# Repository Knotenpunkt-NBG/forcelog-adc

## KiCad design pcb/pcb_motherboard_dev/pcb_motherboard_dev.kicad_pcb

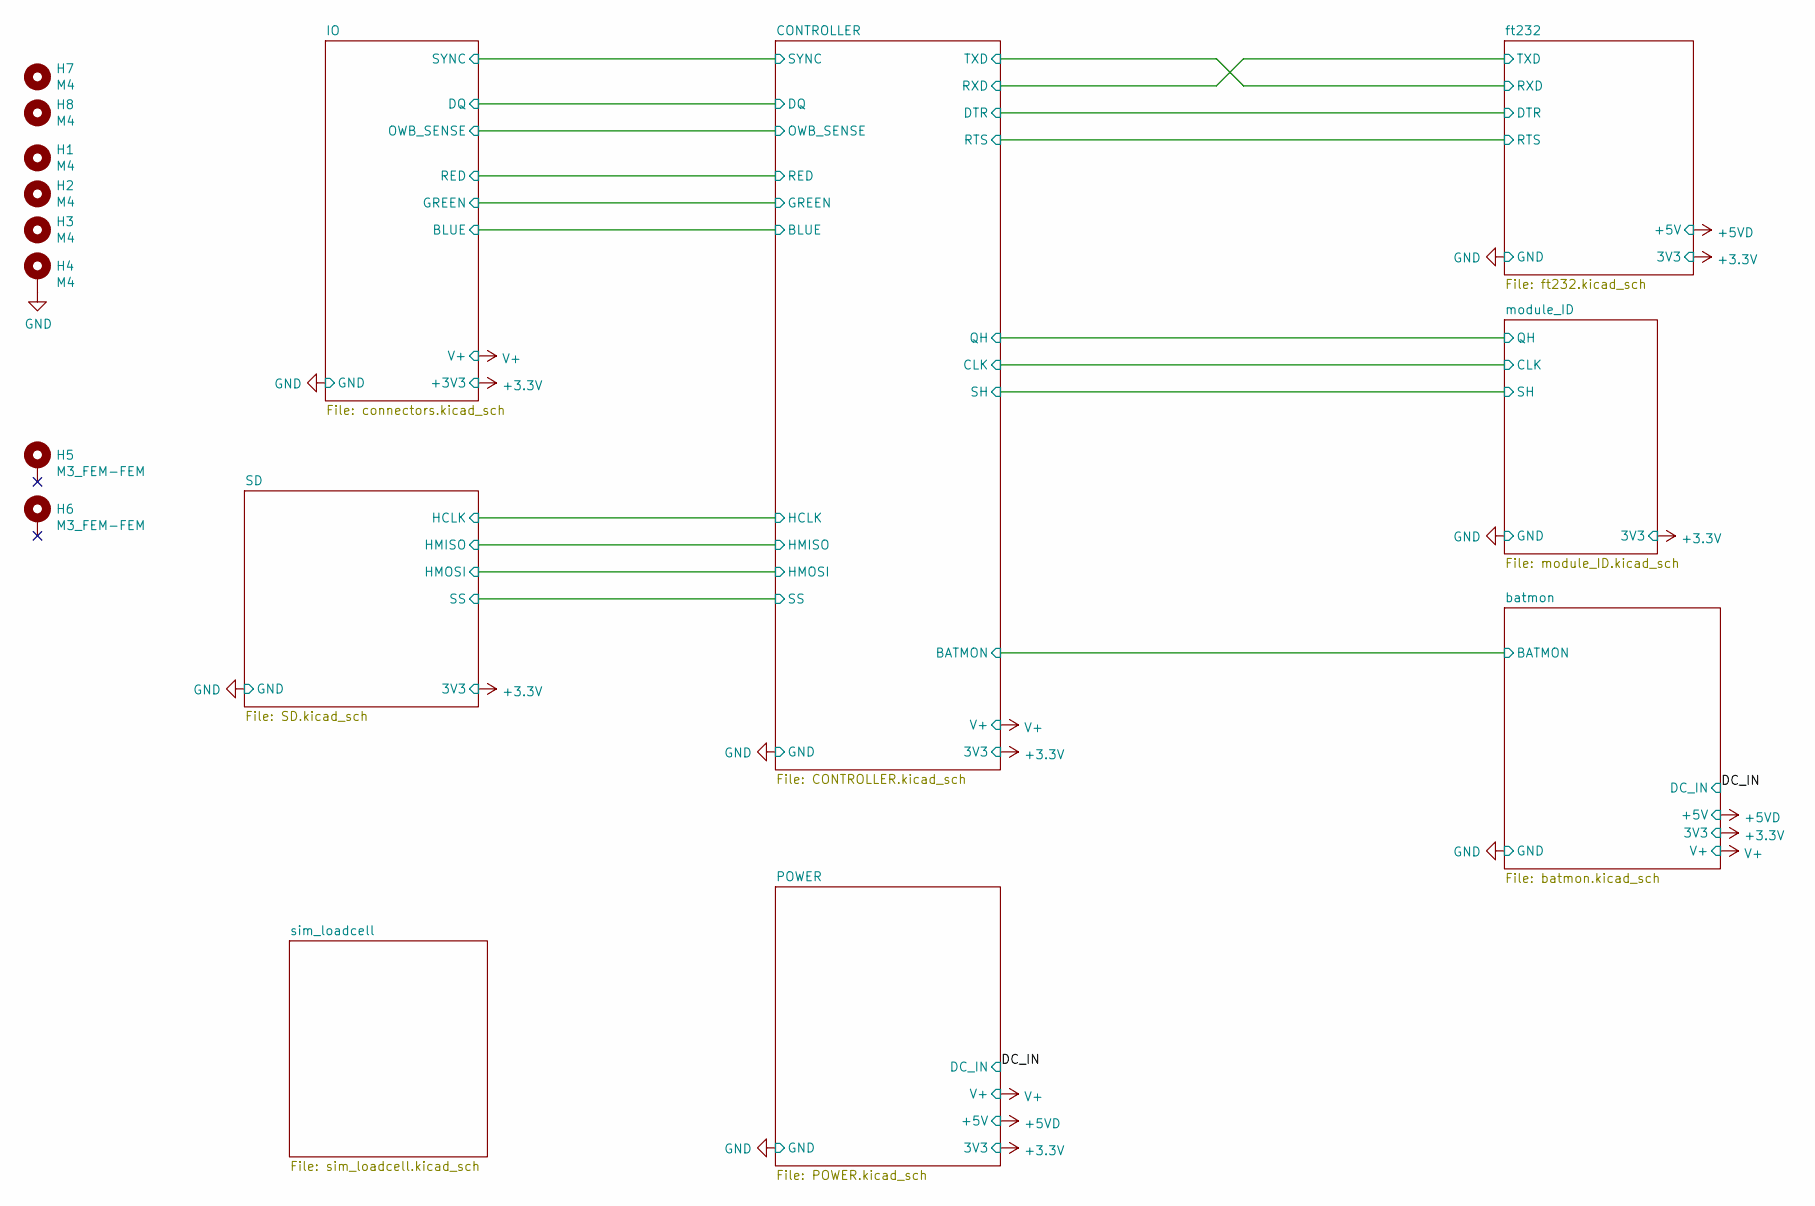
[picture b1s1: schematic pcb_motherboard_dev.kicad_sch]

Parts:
H1, H7: M4; MountingHole_4.3mm_M4_Pad_Via
H2, H3, H4, H8: M4; MountingHole_3.2mm_M3_Pad_Via
H5, H6: M3_FEM-FEM; MountingHole_3.2mm_M3_Pad_Via

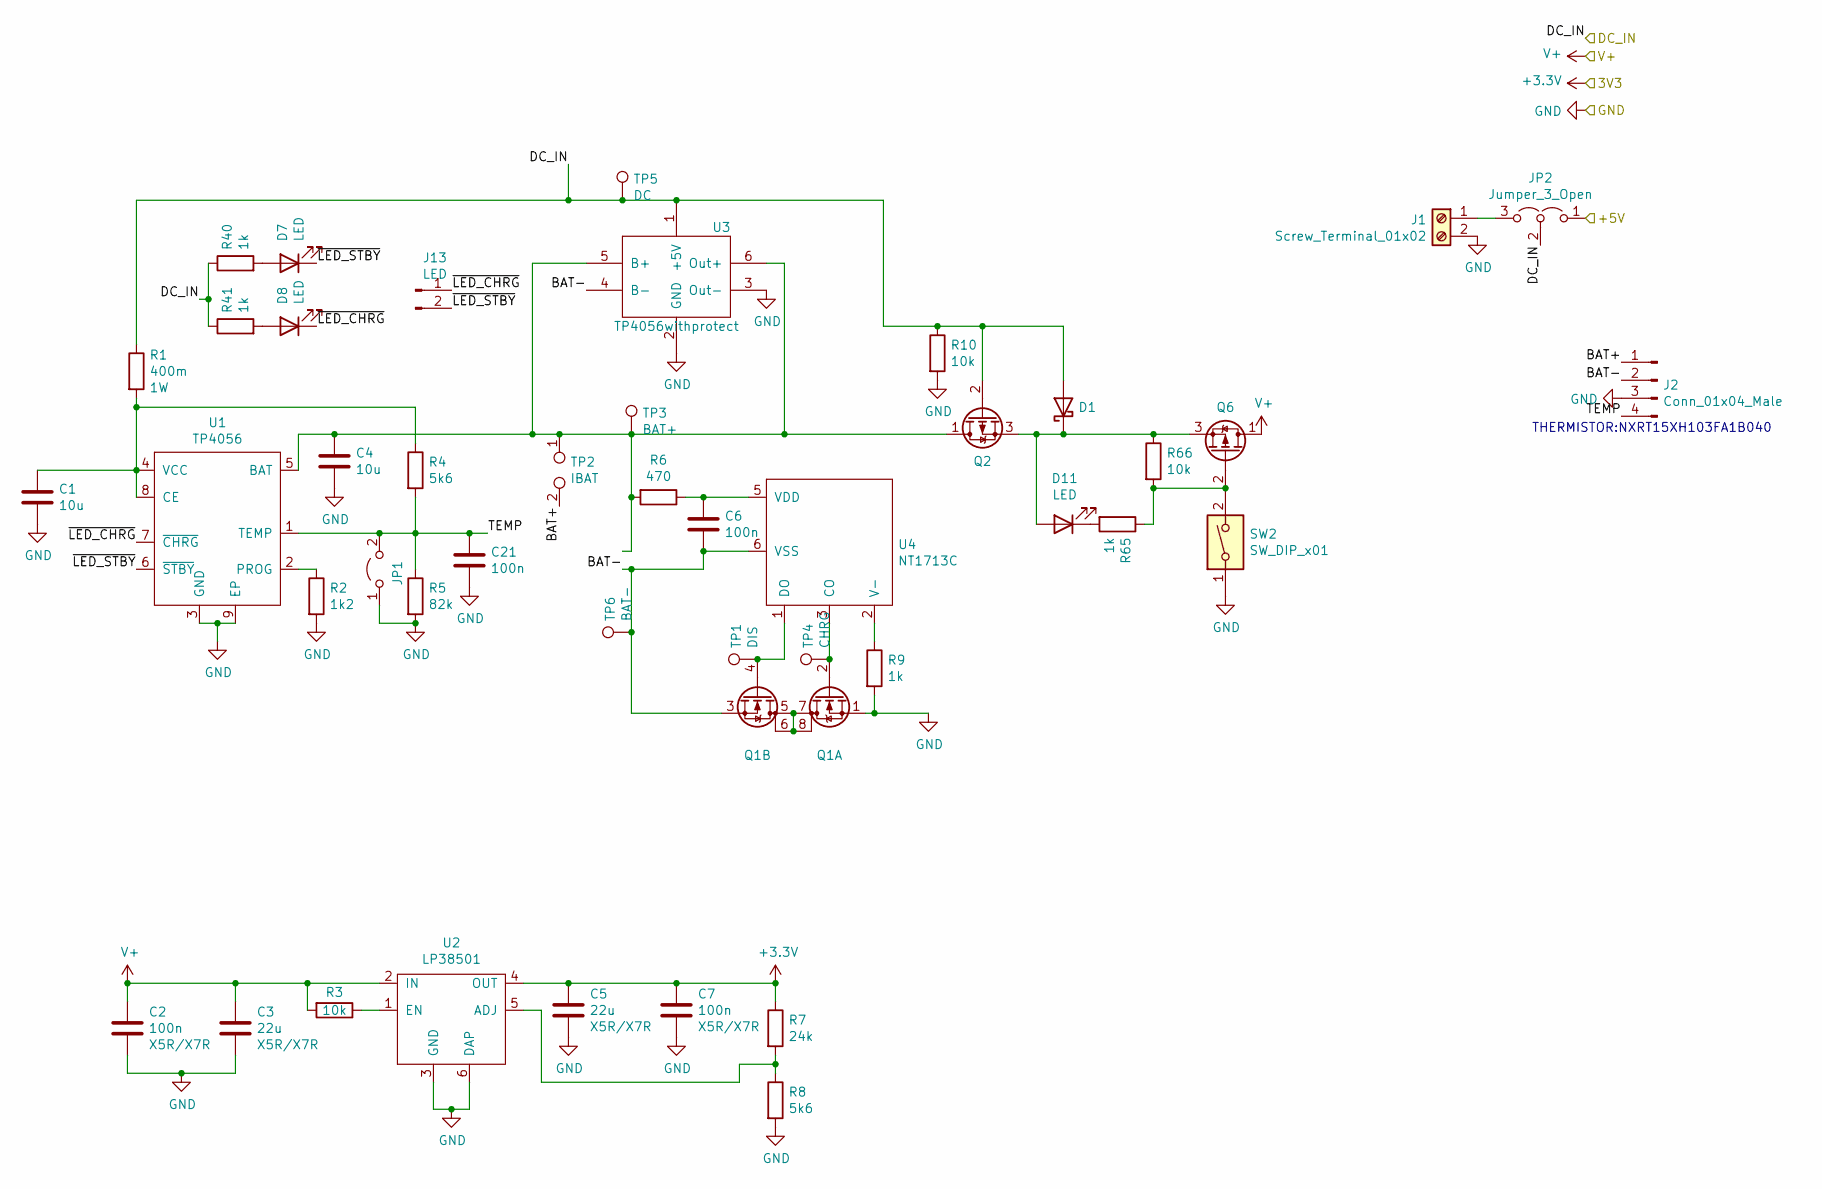
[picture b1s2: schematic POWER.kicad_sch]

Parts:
C1, C4: 10u; C_1206_3216Metric_Pad1.33x1.80mm_HandSolder; Digikey 1276-1075-1-ND
C2, C6, C7, C21: 100n; C_1206_3216Metric_Pad1.33x1.80mm_HandSolder; Digikey 399-C1206C104K5RAC7800CT-ND
C3, C5: 22u; C_1206_3216Metric_Pad1.33x1.80mm_HandSolder; Digikey 1276-2728-1-ND
D1: PMEG3030EP,115; D_SOD-128; Digikey 1727-5324-1-ND
D7, D11: LED; LED_1206_3216Metric_Pad1.42x1.75mm_HandSolder; Digikey 732-5032-1-ND
D8: LED; LED_1206_3216Metric_Pad1.42x1.75mm_HandSolder; Digikey 732-5034-1-ND
J1: Screw_Terminal_01x02; TerminalBlock_Phoenix_MKDS-1,5-2_1x02_P5.00mm_Horizontal; Digikey 277-16667-ND
J2: Conn_01x04_Male; JST_XH_S4B-XH-A-1_1x04_P2.50mm_Horizontal; Digikey 455-4227-ND
J13: LED; TestPoint_2Pads_Pitch2.54mm_Drill0.8mm
JP1: Jumper_2_Open; PinHeader_1x02_P2.54mm_Vertical
JP2: Jumper_3_Open; PinHeader_1x03_P2.54mm_Vertical
Q1: DMG9926USD; SO-8_3.9x4.9mm_P1.27mm; Digikey DMG9926USD-13DICT-ND
Q2, Q6: IRF7410TRPBF; SO8_3.8x4.8_SSSGDDDD; Digikey IRF7410TRPBF
R1: 400m; R_2512_6332Metric_Pad1.40x3.35mm_HandSolder; LCSC C165323
R2: 1k2; R_1206_3216Metric_Pad1.30x1.75mm_HandSolder; LCSC C185265
R3, R10, R66: 10k; R_1206_3216Metric_Pad1.30x1.75mm_HandSolder; LCSC C132649
R4, R8: 5k6; R_1206_3216Metric_Pad1.30x1.75mm_HandSolder; LCSC C137248
R5: 82k; R_1206_3216Metric_Pad1.30x1.75mm_HandSolder; LCSC C137229
R6: 470; R_1206_3216Metric_Pad1.30x1.75mm_HandSolder; LCSC C114945
R7: 24k; R_1206_3216Metric_Pad1.30x1.75mm_HandSolder; LCSC C163384
R9, R40, R41, R65: 1k; R_1206_3216Metric_Pad1.30x1.75mm_HandSolder; LCSC C131398
SW2: SW_DIP_x01; SW_DIP_SPSTx01_Slide_9.78x4.72mm_W7.62mm_P2.54mm; LCSC C229812
TP1: DIS; PinHeader_1x01_P2.54mm_Vertical
TP2: IBAT; PinHeader_1x02_P2.54mm_Vertical
TP3: BAT+; PinHeader_1x01_P2.54mm_Vertical
TP4: CHRG; PinHeader_1x01_P2.54mm_Vertical
TP5: DC; PinHeader_1x01_P2.54mm_Vertical
TP6: BAT-; PinHeader_1x01_P2.54mm_Vertical
U1: TP4056; SOIC-8-1EP_3.9x4.9mm_P1.27mm_EP2.29x3mm_ThermalVias; LCSC C191323
U2: LP38501; TO-263-5_TabPin6; LCSC C779671
U3: TP4056withprotect; TP4056_module_prot; Digikey N/A
U4: NT1713C; SOT-23-6_Handsoldering; LCSC C596362

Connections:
+5V: JP2.1 (A); also elsewhere on the board
/DC_IN: D1.2 (A), JP2.2 (C), Q2.2 (G), R1.1, R10.1, R40.1, R41.1, TP5.1, U3.1 (+5V); also elsewhere on the board
/POWER/BAT+: J2.1, TP2.2
/POWER/BAT-: C6.2, J2.2, Q1.3 (S), TP6.1, U3.4 (B-), U4.6 (VSS)
/POWER/TEMP: C21.1, J2.4, JP1.2 (B), R4.2, R5.1, U1.1 (TEMP)
/POWER/~LED_CHRG: D8.1 (K), J13.1, U1.7 (~CHRG)
/POWER/~LED_STBY: D7.1 (K), J13.2, U1.6 (~STBY)
unnamed: C1.1, R1.2, R4.1, U1.4 (VCC), U1.8 (CE)
unnamed: C4.1, Q2.1 (D), R6.2, TP2.1, TP3.1, U1.5 (BAT), U3.5 (B+), U3.6 (Out+)
unnamed: C6.1, R6.1, U4.5 (VDD)
unnamed: D1.1 (K), D11.2 (A), Q2.3 (S), Q6.3 (S), R66.1
unnamed: D7.2 (A), R40.2
unnamed: D8.2 (A), R41.2
unnamed: D11.1 (K), R65.2
unnamed: J1.1, JP2.3 (B)
unnamed: Q1.2 (G), TP4.1, U4.3 (CO)
unnamed: Q1.4 (G), TP1.1, U4.1 (DO)
unnamed: Q1.5 (D), Q1.6 (D), Q1.7 (D), Q1.8 (D)
unnamed: Q6.2 (G), R65.1, R66.2, SW2.2
unnamed: R2.1, U1.2 (PROG)
unnamed: R3.1, U2.1 (EN)
unnamed: R7.2, R8.1, U2.5 (ADJ)
unnamed: R9.1, U4.2 (V-)
V+: C2.1, C3.1, Q6.1 (D), R3.2, U2.2 (IN); also elsewhere on the board

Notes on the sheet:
THERMISTOR:NXRT15XH103FA1B040

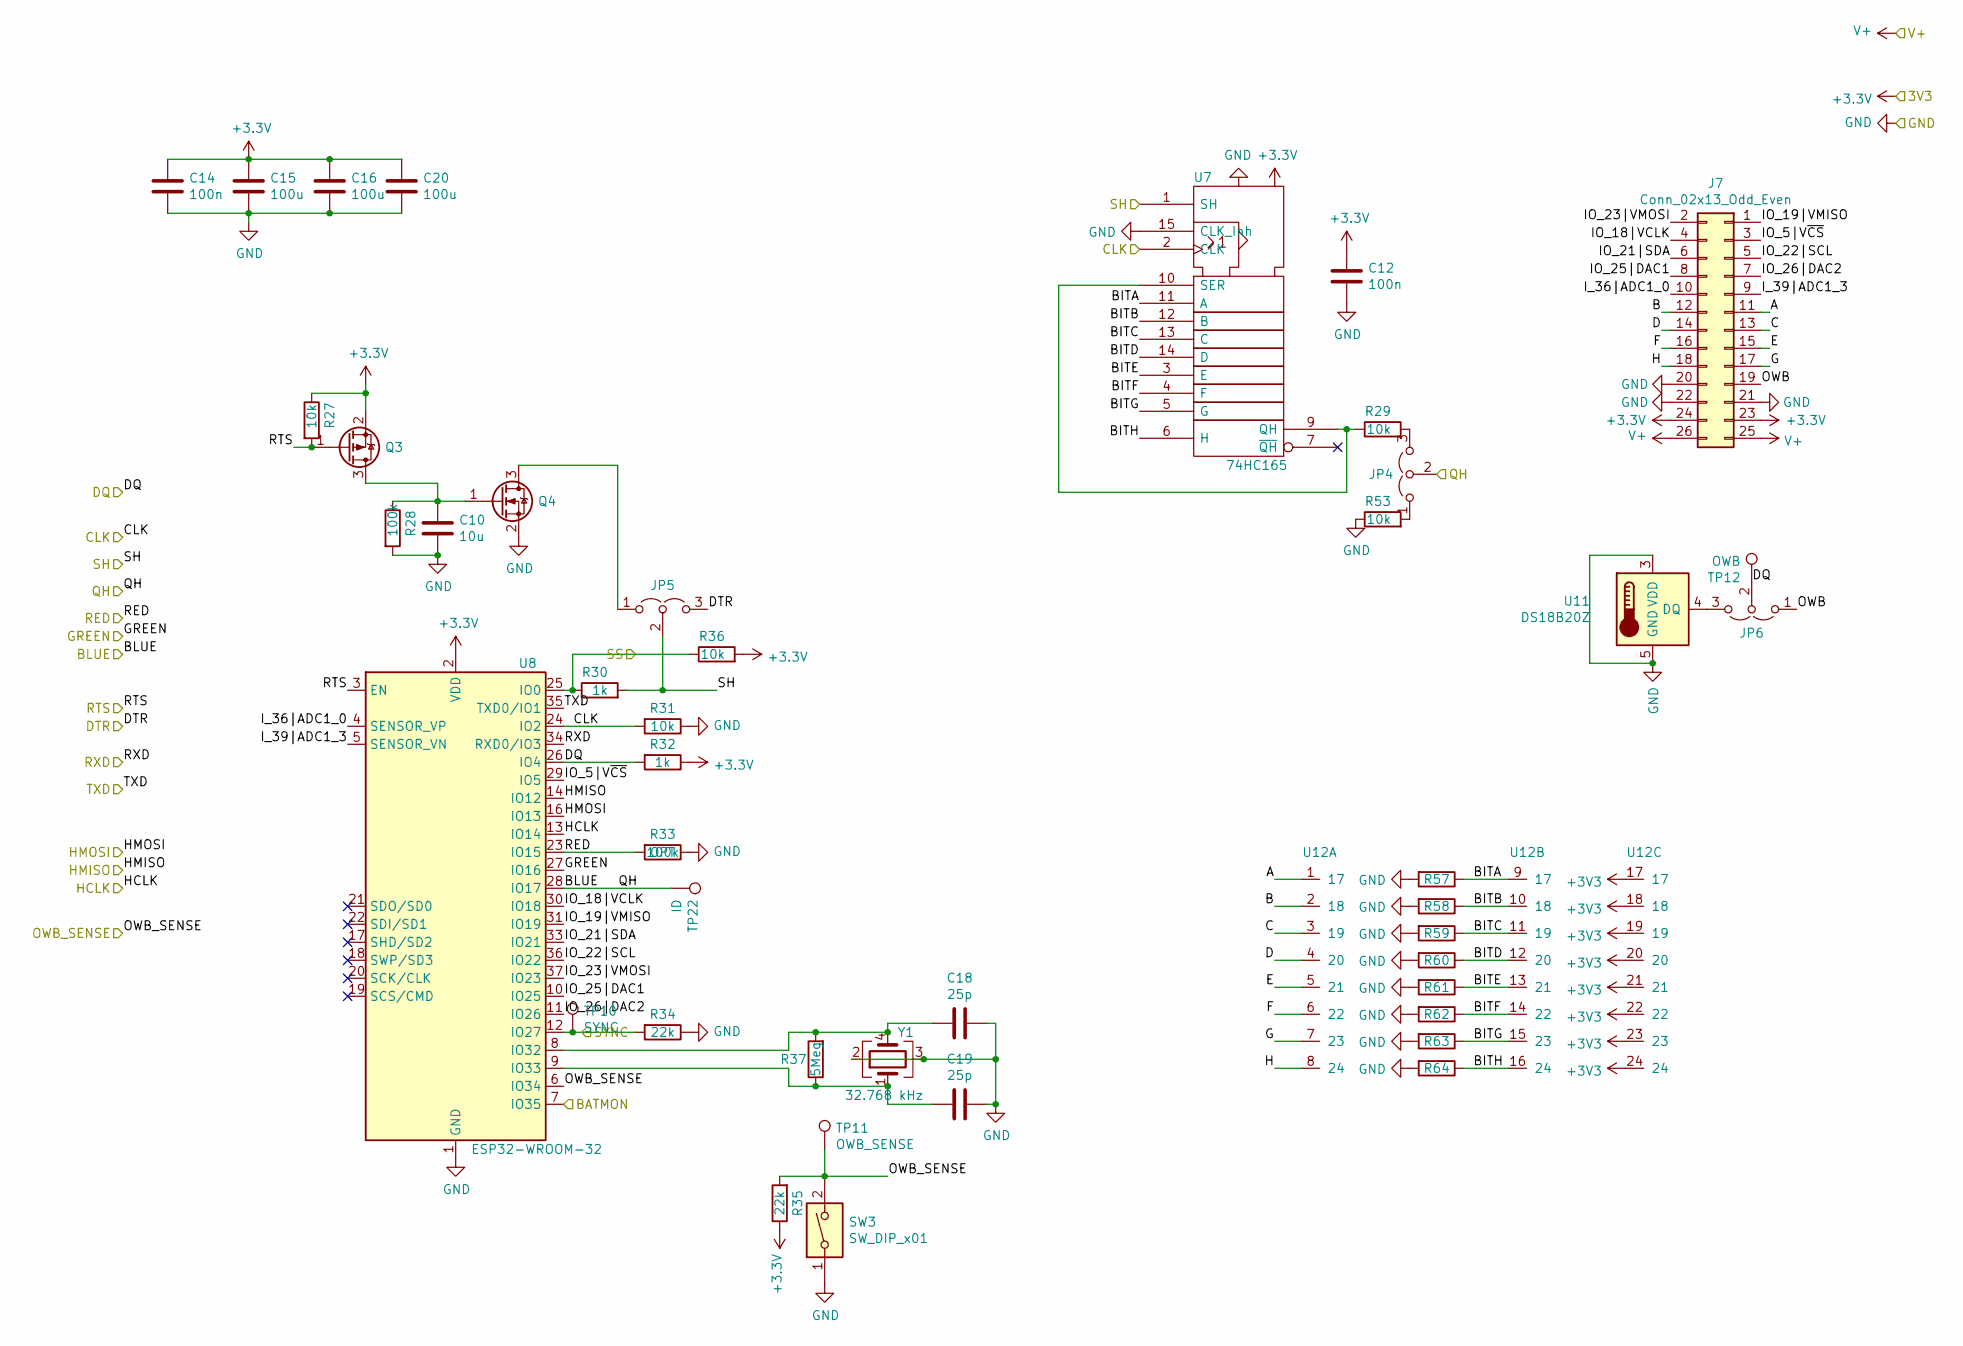
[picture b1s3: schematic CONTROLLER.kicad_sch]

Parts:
C10: 10u; C_1206_3216Metric_Pad1.33x1.80mm_HandSolder
C12, C14: 100n; C_1206_3216Metric_Pad1.33x1.80mm_HandSolder; Digikey 399-C1206C104K5RAC7800CT-ND
C15: 100u; C_1206_3216Metric_Pad1.33x1.80mm_HandSolder; Digikey 1276-1782-1-ND
C16, C20: 100u; C_1206_3216Metric_Pad1.33x1.80mm_HandSolder; LCSC C312983
C18, C19: 25p; C_1206_3216Metric_Pad1.33x1.80mm_HandSolder; Digikey N/A
J7: Conn_02x13_Odd_Even; PinSocket_2x13_P2.54mm_Vertical; LCSC C35165
JP4, JP5, JP6: Jumper_3_Open; PinHeader_1x03_P2.54mm_Vertical
Q3: IRLML2244TRPBF; SOT-23; Digikey IRLML2244TRPBFCT-ND
Q4: BSS806NE; SOT-23; LCSC C91714
R27, R29, R31, R36, R53, R57, R58, R59, R60, R61, R62, R63, R64: 10k; R_1206_3216Metric_Pad1.30x1.75mm_HandSolder; LCSC C132649
R28: 100k; R_1206_3216Metric_Pad1.30x1.75mm_HandSolder
R30, R32: 1k; R_1206_3216Metric_Pad1.30x1.75mm_HandSolder; LCSC C131398
R33: 100k; R_1206_3216Metric_Pad1.30x1.75mm_HandSolder; LCSC C137393
R34: 22k; R_1206_3216Metric_Pad1.30x1.75mm_HandSolder; LCSC C229456
R35: 22k; R_1206_3216Metric_Pad1.30x1.75mm_HandSolder; LCSC C132649
R37: 5Meg; R_1206_3216Metric_Pad1.30x1.75mm_HandSolder; LCSC C163371
SW3: SW_DIP_x01; SW_DIP_SPSTx01_Slide_9.78x4.72mm_W7.62mm_P2.54mm; LCSC C229812
TP10: SYNC; PinHeader_1x01_P2.54mm_Vertical
TP11: OWB_SENSE; PinHeader_1x01_P2.54mm_Vertical
TP12: OWB; PinHeader_1x01_P2.54mm_Vertical
TP22: ID; PinHeader_1x01_P2.54mm_Vertical
U7: 74HC165; SO-16_3.9x9.9mm_P1.27mm; LCSC C7334
U8: ESP32-WROOM-32; ESP32-WROOM-BREAKOUT
U11: DS18B20Z; SOIC-8_3.9x4.9mm_P1.27mm; LCSC C97190
U12: 2POS_JUMPER_8BIT
Y1: 32.768 kHz; Crystal_SMD_SeikoEpson_MC306-4Pin_8.0x3.2mm_HandSoldering; Digikey 300-8742-1-ND

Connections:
/CONTROLLER/A: J7.11, U12.1 (17)
/CONTROLLER/B: J7.12, U12.2 (18)
/CONTROLLER/BATMON: U8.7 (IO35); also elsewhere on the board
/CONTROLLER/BITA: R57.1, U7.11 (A), U12.9 (17)
/CONTROLLER/BITB: R58.1, U7.12 (B), U12.10 (18)
/CONTROLLER/BITC: R59.1, U7.13 (C), U12.11 (19)
/CONTROLLER/BITD: R60.1, U7.14 (D), U12.12 (20)
/CONTROLLER/BITE: R61.1, U7.3 (E), U12.13 (21)
/CONTROLLER/BITF: R62.1, U7.4 (F), U12.14 (22)
/CONTROLLER/BITG: R63.1, U7.5 (G), U12.15 (23)
/CONTROLLER/BITH: R64.1, U7.6 (H), U12.16 (24)
/CONTROLLER/BLUE: JP4.2 (C), TP22.1, U8.28 (IO17); also elsewhere on the board
/CONTROLLER/C: J7.13, U12.3 (19)
/CONTROLLER/CLK: R31.2, U7.2 (CLK), U8.24 (IO2)
/CONTROLLER/D: J7.14, U12.4 (20)
/CONTROLLER/DQ: JP6.2 (C), R32.2, TP12.1, U8.26 (IO4); also elsewhere on the board
/CONTROLLER/DTR: JP5.3 (B); also elsewhere on the board
/CONTROLLER/E: J7.15, U12.5 (21)
/CONTROLLER/F: J7.16, U12.6 (22)
/CONTROLLER/G: J7.17, U12.7 (23)
/CONTROLLER/GREEN: U8.27 (IO16); also elsewhere on the board
/CONTROLLER/H: J7.18, U12.8 (24)
/CONTROLLER/HCLK: U8.13 (IO14); also elsewhere on the board
/CONTROLLER/HMISO: U8.14 (IO12); also elsewhere on the board
/CONTROLLER/HMOSI: U8.16 (IO13); also elsewhere on the board
/CONTROLLER/IO_5|V~CS: J7.3, U8.29 (IO5)
/CONTROLLER/IO_18|VCLK: J7.4, U8.30 (IO18)
/CONTROLLER/IO_19|VMISO: J7.1, U8.31 (IO19)
/CONTROLLER/IO_21|SDA: J7.6, U8.33 (IO21)
/CONTROLLER/IO_22|SCL: J7.5, U8.36 (IO22)
/CONTROLLER/IO_23|VMOSI: J7.2, U8.37 (IO23)
/CONTROLLER/IO_25|DAC1: J7.8, U8.10 (IO25)
/CONTROLLER/IO_26|DAC2: J7.7, U8.11 (IO26)
/CONTROLLER/I_36|ADC1_0: J7.10, U8.4 (SENSOR_VP)
/CONTROLLER/I_39|ADC1_3: J7.9, U8.5 (SENSOR_VN)
/CONTROLLER/OWB: J7.19, JP6.1 (A)
/CONTROLLER/OWB_SENSE: R35.2, SW3.2, TP11.1, U8.6 (IO34); also elsewhere on the board
/CONTROLLER/RED: R33.2, U8.23 (IO15); also elsewhere on the board
/CONTROLLER/RTS: Q3.1 (G), R27.2, U8.3 (EN); also elsewhere on the board
/CONTROLLER/RXD: U8.34 (RXD0/IO3); also elsewhere on the board
/CONTROLLER/SH: JP5.2 (C), R30.2, U7.1 (SH)
/CONTROLLER/SS: R30.1, R36.1, U8.25 (IO0); also elsewhere on the board
/CONTROLLER/SYNC: R34.2, TP10.1, U8.12 (IO27); also elsewhere on the board
/ft232/RXD: U8.35 (TXD0/IO1); also elsewhere on the board
unnamed: C10.1, Q3.3 (D), Q4.1 (G), R28.1
unnamed: C18.2, R37.2, U8.8 (IO32), Y1.4
unnamed: C19.1, R37.1, U8.9 (IO33), Y1.1
unnamed: JP4.1 (A), R53.2
unnamed: JP4.3 (B), R29.2
unnamed: JP5.1 (A), Q4.3 (D)
unnamed: JP6.3 (B), U11.4 (DQ)
unnamed: R29.1, U7.9 (QH), U7.10 (SER)
V+: J7.25, J7.26; also elsewhere on the board

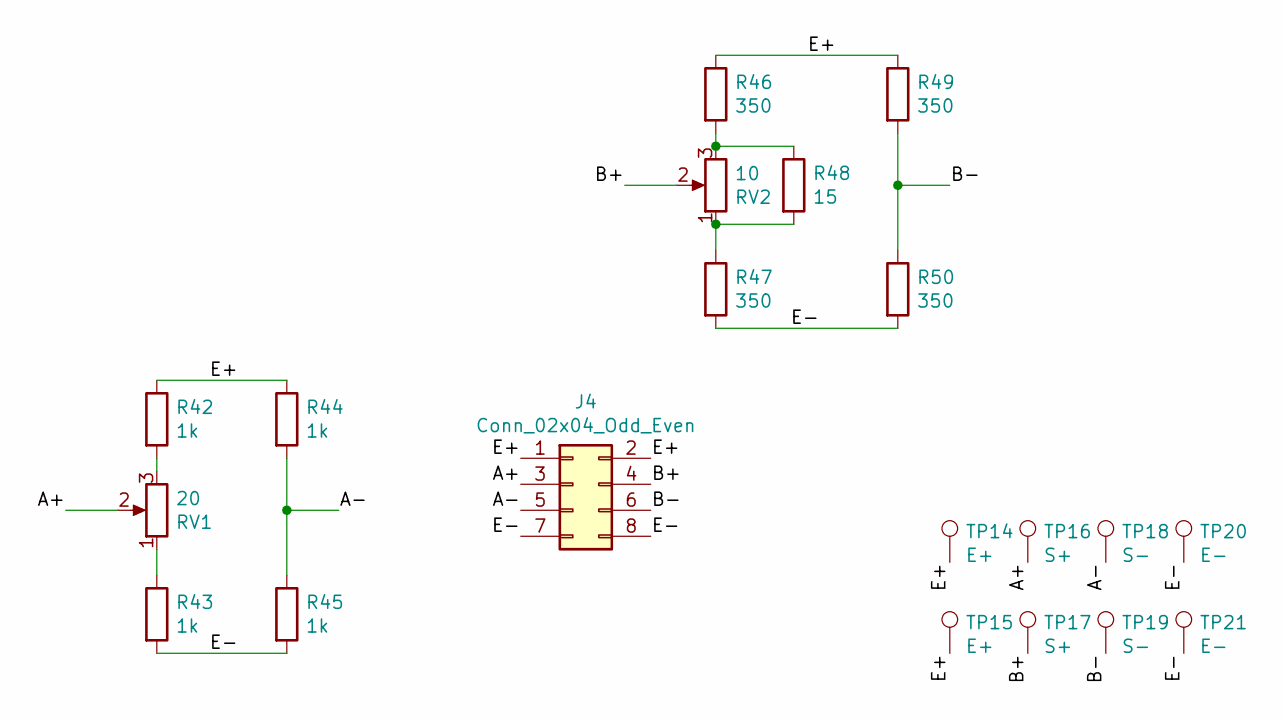
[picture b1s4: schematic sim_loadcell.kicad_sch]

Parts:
J4: Conn_02x04_Odd_Even; PinHeader_2x04_P2.54mm_Horizontal; LCSC C358706
R42, R43, R44, R45: 1k; R_1206_3216Metric_Pad1.30x1.75mm_HandSolder; LCSC C131398
R46, R47, R49, R50: 350; R_1206_3216Metric_Pad1.30x1.75mm_HandSolder; LCSC C163378
R48: 15; R_1206_3216Metric_Pad1.30x1.75mm_HandSolder; LCSC C137386
RV1: 20; Potentiometer_Bourns_3386P_Vertical; Digikey 3386P-1-200TLF-ND
RV2: 10; Potentiometer_Bourns_3386P_Vertical; LCSC C116299
TP14, TP15: E+; PinHeader_1x01_P2.54mm_Vertical
TP16, TP17: S+; PinHeader_1x01_P2.54mm_Vertical
TP18, TP19: S-; PinHeader_1x01_P2.54mm_Vertical
TP20, TP21: E-; PinHeader_1x01_P2.54mm_Vertical

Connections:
/sim_loadcell/A+: J4.3, RV1.2, TP16.1
/sim_loadcell/A-: J4.5, R44.2, R45.1, TP18.1
/sim_loadcell/B+: J4.4, RV2.2, TP17.1
/sim_loadcell/B-: J4.6, R49.2, R50.1, TP19.1
/sim_loadcell/E+: J4.1, J4.2, R42.1, R44.1, R46.1, R49.1, TP14.1, TP15.1
/sim_loadcell/E-: J4.7, J4.8, R43.2, R45.2, R47.2, R50.2, TP20.1, TP21.1
unnamed: R42.2, RV1.3
unnamed: R43.1, RV1.1
unnamed: R46.2, R48.1, RV2.3
unnamed: R47.1, R48.2, RV2.1

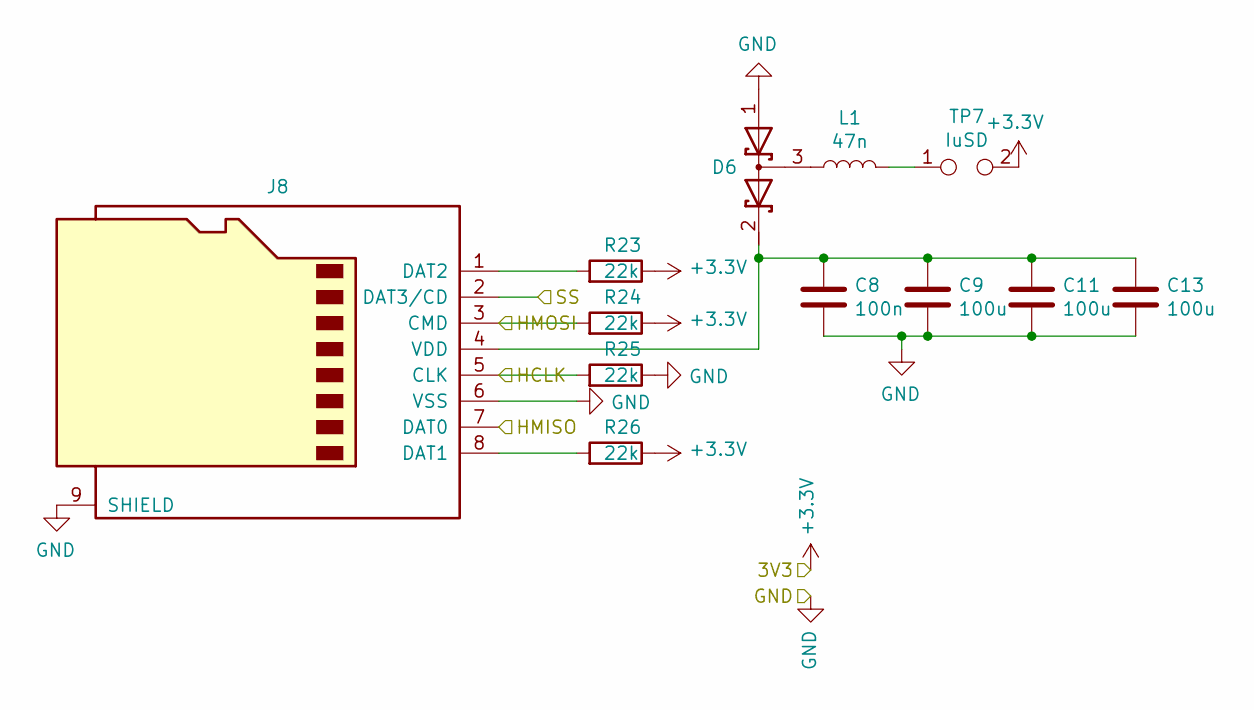
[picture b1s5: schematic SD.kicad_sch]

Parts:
C8: 100n; C_1206_3216Metric_Pad1.33x1.80mm_HandSolder; Digikey 399-C1206C104K5RAC7800CT-ND
C9: 100u; C_1206_3216Metric_Pad1.33x1.80mm_HandSolder; Digikey 1276-1782-1-ND
C11, C13: 100u; C_1206_3216Metric_Pad1.33x1.80mm_HandSolder; LCSC C312983
D6: BAT54S; SOT-23; Digikey 1727-1868-1-ND
J8: Micro_SD_Card; uSD_Molex_0472192001; Partnumber 472192001; Digikey WM6698CT-ND
L1: 47n; L_1210_3225Metric_Pad1.42x2.65mm_HandSolder; Digikey 445-16541-1-ND
R23, R24, R25, R26: 22k; R_1206_3216Metric_Pad1.30x1.75mm_HandSolder; LCSC C229456
TP7: IuSD; PinHeader_1x02_P2.54mm_Vertical

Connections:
/CONTROLLER/HCLK: J8.5 (CLK), R25.2; also elsewhere on the board
/CONTROLLER/HMISO: J8.7 (DAT0); also elsewhere on the board
/CONTROLLER/HMOSI: J8.3 (CMD), R24.2; also elsewhere on the board
/CONTROLLER/SS: J8.2 (DAT3/CD); also elsewhere on the board
unnamed: C8.1, C9.1, C11.1, C13.1, D6.2 (K), J8.4 (VDD)
unnamed: D6.3 (common), L1.1
unnamed: J8.1 (DAT2), R23.2
unnamed: J8.8 (DAT1), R26.2
unnamed: L1.2, TP7.1

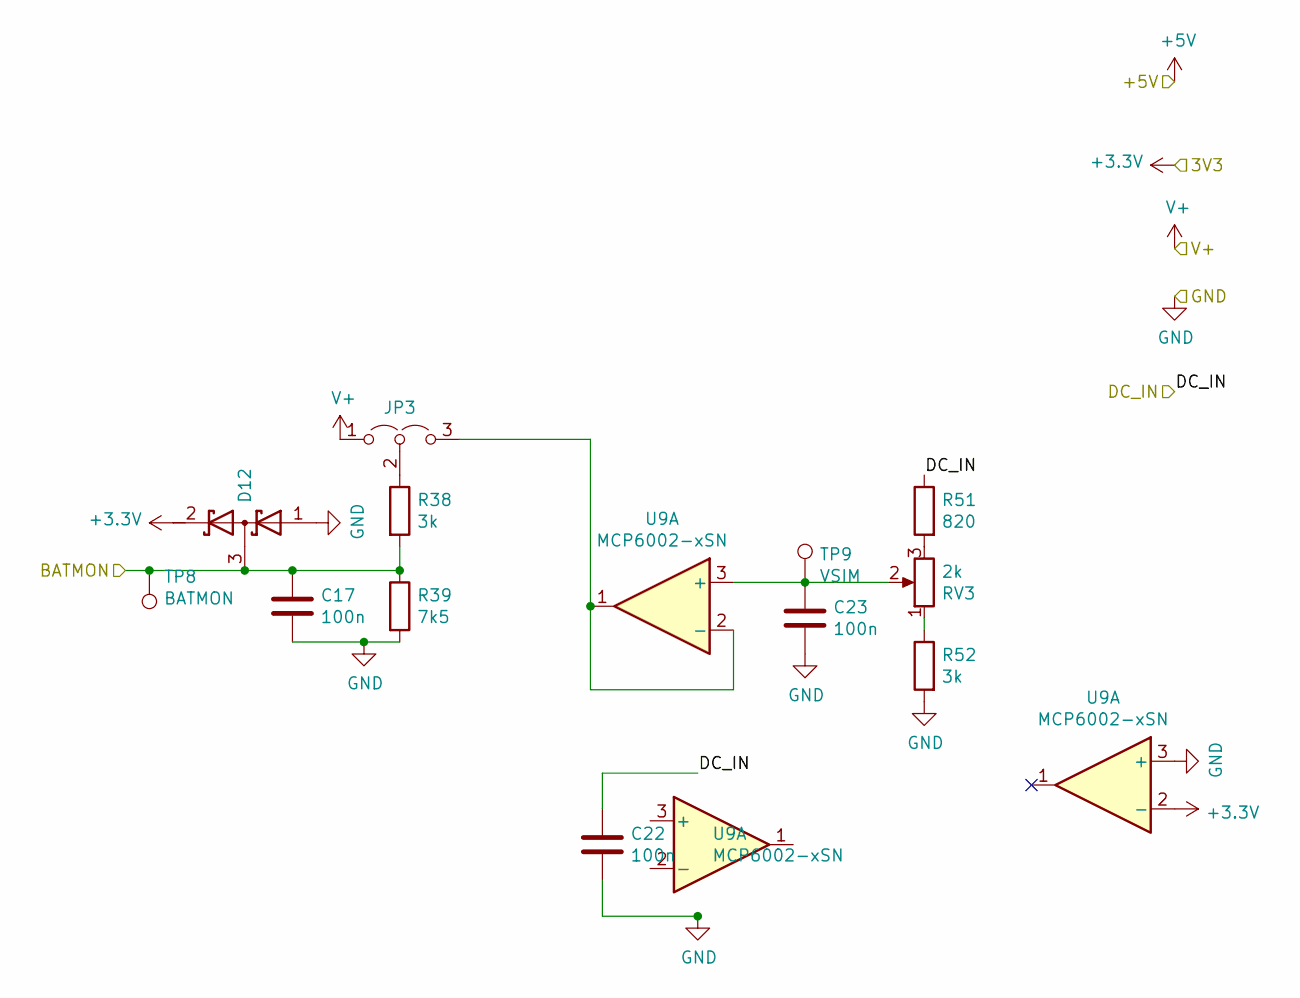
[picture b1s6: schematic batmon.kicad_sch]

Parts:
C17, C22, C23: 100n; C_1206_3216Metric_Pad1.33x1.80mm_HandSolder; Digikey 399-C1206C104K5RAC7800CT-ND
D12: BAT54S; SOT-23; Digikey 1727-1868-1-ND
JP3: Jumper_3_Open; PinHeader_1x03_P2.54mm_Vertical
R38, R52: 3k; R_1206_3216Metric_Pad1.30x1.75mm_HandSolder; LCSC C132648
R39: 7k5; R_1206_3216Metric_Pad1.30x1.75mm_HandSolder; LCSC C137232
R51: 820; R_1206_3216Metric_Pad1.30x1.75mm_HandSolder; LCSC C229812
RV3: 2k; Potentiometer_Bourns_3296W_Vertical; LCSC C118206
TP8: BATMON; PinHeader_1x01_P2.54mm_Vertical
TP9: VSIM; PinHeader_1x01_P2.54mm_Vertical
U9: MCP6002-xSN; SO-8_3.9x4.9mm_P1.27mm; LCSC C7377

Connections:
/CONTROLLER/BATMON: C17.1, D12.3 (common), R38.2, R39.1, TP8.1; also elsewhere on the board
/DC_IN: C22.1, R51.1, U9.8 (V+); also elsewhere on the board
unnamed: JP3.2 (C), R38.1
unnamed: R51.2, RV3.3
unnamed: R52.1, RV3.1
V+: JP3.1 (A); also elsewhere on the board

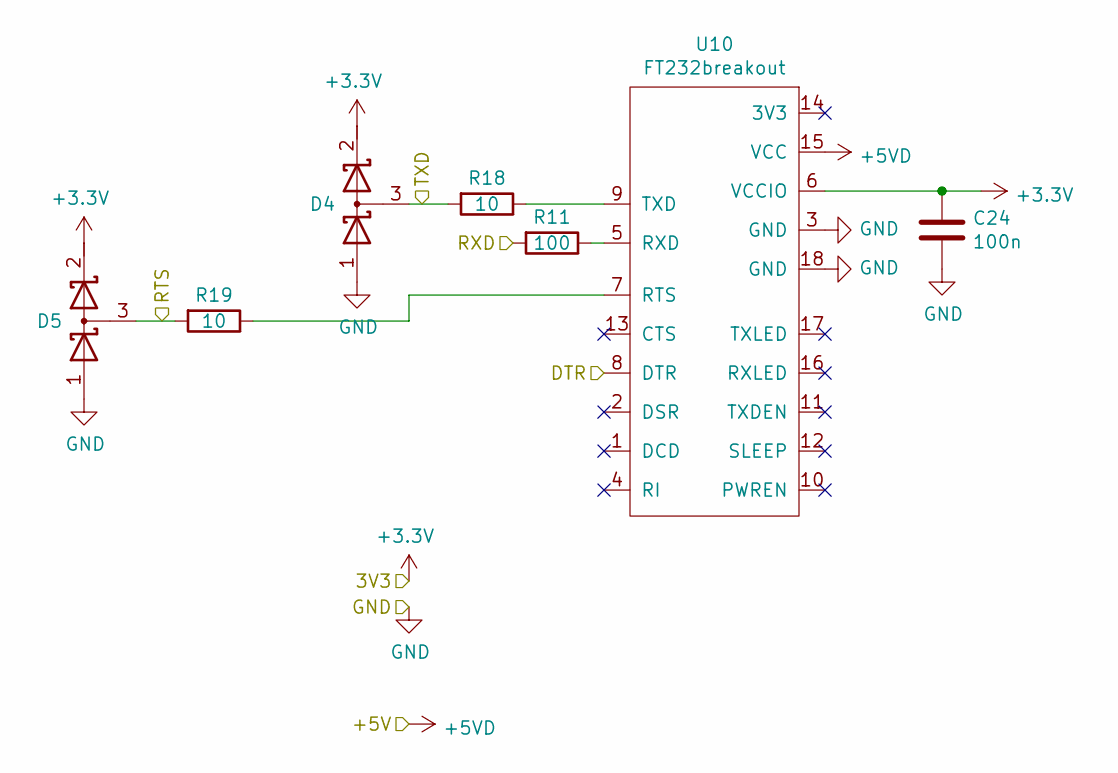
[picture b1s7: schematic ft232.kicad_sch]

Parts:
C24: 100n; C_1206_3216Metric_Pad1.33x1.80mm_HandSolder; Digikey 399-C1206C104K5RAC7800CT-ND
D4, D5: BAT54S; SOT-23; Digikey 1727-1868-1-ND
R11: 100; R_1206_3216Metric_Pad1.30x1.75mm_HandSolder; LCSC C137392
R18, R19: 10; R_1206_3216Metric_Pad1.30x1.75mm_HandSolder; LCSC C108080
U10: FT232breakout; ft232rl_breakout_combined_flipped

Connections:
+5V: U10.15 (VCC); also elsewhere on the board
/CONTROLLER/DTR: U10.8 (DTR); also elsewhere on the board
/CONTROLLER/RTS: D5.3 (common), R19.2; also elsewhere on the board
/CONTROLLER/RXD: D4.3 (common), R18.2; also elsewhere on the board
/ft232/RXD: R11.2; also elsewhere on the board
unnamed: R11.1, U10.5 (RXD)
unnamed: R18.1, U10.9 (TXD)
unnamed: R19.1, U10.7 (RTS)

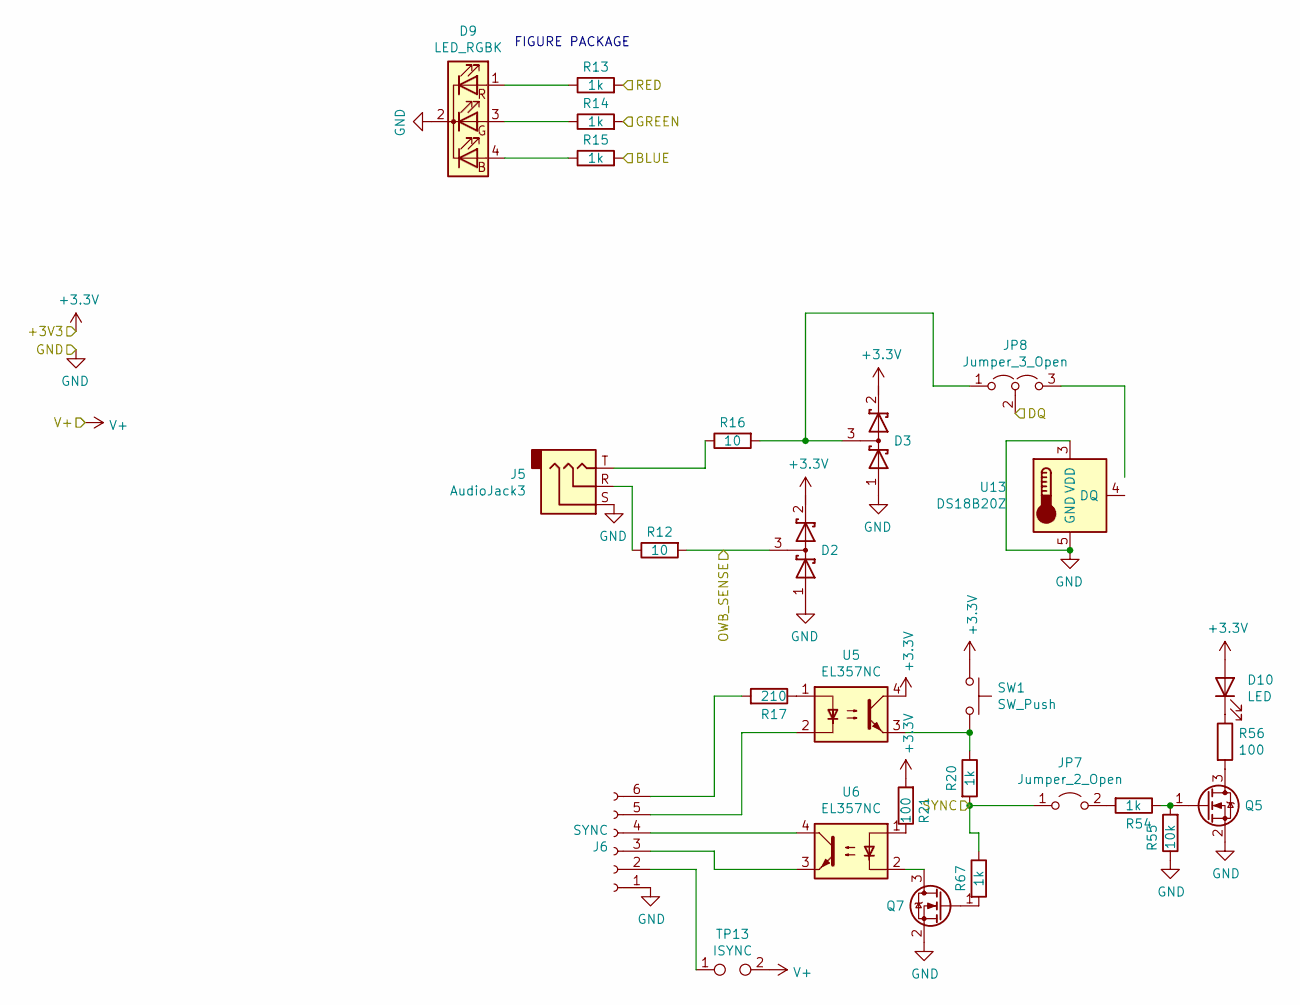
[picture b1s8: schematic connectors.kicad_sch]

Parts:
D2, D3: BAT54S; SOT-23; Digikey 1727-1868-1-ND
D9: LED_RGBK; LED_D5.0mm-4_RGB; LCSC C330759
D10: LED; LED_1206_3216Metric_Pad1.42x1.75mm_HandSolder; Digikey 732-4989-1-ND
J5: AudioJack3; 3.5mm_audio_PJ-3126-C; Digikey CP1-3523N-ND
J6: SYNC; TerminalBlock_Phoenix_MKDS-1,5-6_1x06_P5.00mm_Horizontal; LCSC C8379
JP7: Jumper_2_Open; PinHeader_1x02_P2.54mm_Vertical
JP8: Jumper_3_Open; PinHeader_1x03_P2.54mm_Vertical
Q5, Q7: BSS806NE; SOT-23; LCSC C91714
R12, R16: 10; R_1206_3216Metric_Pad1.30x1.75mm_HandSolder; LCSC C108080
R13, R14, R15, R20, R54, R67: 1k; R_1206_3216Metric_Pad1.30x1.75mm_HandSolder; LCSC C131398
R17: 210; R_1206_3216Metric_Pad1.30x1.75mm_HandSolder; LCSC C488733
R21, R56: 100; R_1206_3216Metric_Pad1.30x1.75mm_HandSolder; LCSC C137392
R55: 10k; R_1206_3216Metric_Pad1.30x1.75mm_HandSolder; LCSC C132649
SW1: SW_Push; SW_PUSH_6mm_H8mm; LCSC C294505
TP13: ISYNC; PinHeader_1x02_P2.54mm_Vertical
U5, U6: EL357NC; EL357N; Partnumber EL357N(C)(TA)-VG; Digikey 1080-1601-1-ND
U13: DS18B20Z; SOIC-8_3.9x4.9mm_P1.27mm; LCSC C97190

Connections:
/CONTROLLER/BLUE: R15.2; also elsewhere on the board
/CONTROLLER/DQ: JP8.2 (C); also elsewhere on the board
/CONTROLLER/GREEN: R14.2; also elsewhere on the board
/CONTROLLER/OWB_SENSE: D2.3 (common), R12.2; also elsewhere on the board
/CONTROLLER/RED: R13.2; also elsewhere on the board
/CONTROLLER/SYNC: JP7.1 (A), R20.2, R67.1; also elsewhere on the board
unnamed: D3.3 (common), JP8.1 (A), R16.2
unnamed: D9.1 (RA), R13.1
unnamed: D9.3 (GA), R14.1
unnamed: D9.4 (BA), R15.1
unnamed: D10.1 (K), R56.1
unnamed: J5.R, R12.1
unnamed: J5.T, R16.1
unnamed: J6.2, TP13.1
unnamed: J6.3, U6.3
unnamed: J6.4, U6.4
unnamed: J6.5, U5.2
unnamed: J6.6, R17.2
unnamed: JP7.2 (B), R54.2
unnamed: Q5.1 (G), R54.1, R55.2
unnamed: Q5.3 (D), R56.2
unnamed: Q7.1 (G), R67.2
unnamed: Q7.3 (D), U6.2
unnamed: R17.1, U5.1
unnamed: R20.1, SW1.2, U5.3
unnamed: R21.1, U6.1
V+: TP13.2; also elsewhere on the board

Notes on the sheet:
FIGURE PACKAGE

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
